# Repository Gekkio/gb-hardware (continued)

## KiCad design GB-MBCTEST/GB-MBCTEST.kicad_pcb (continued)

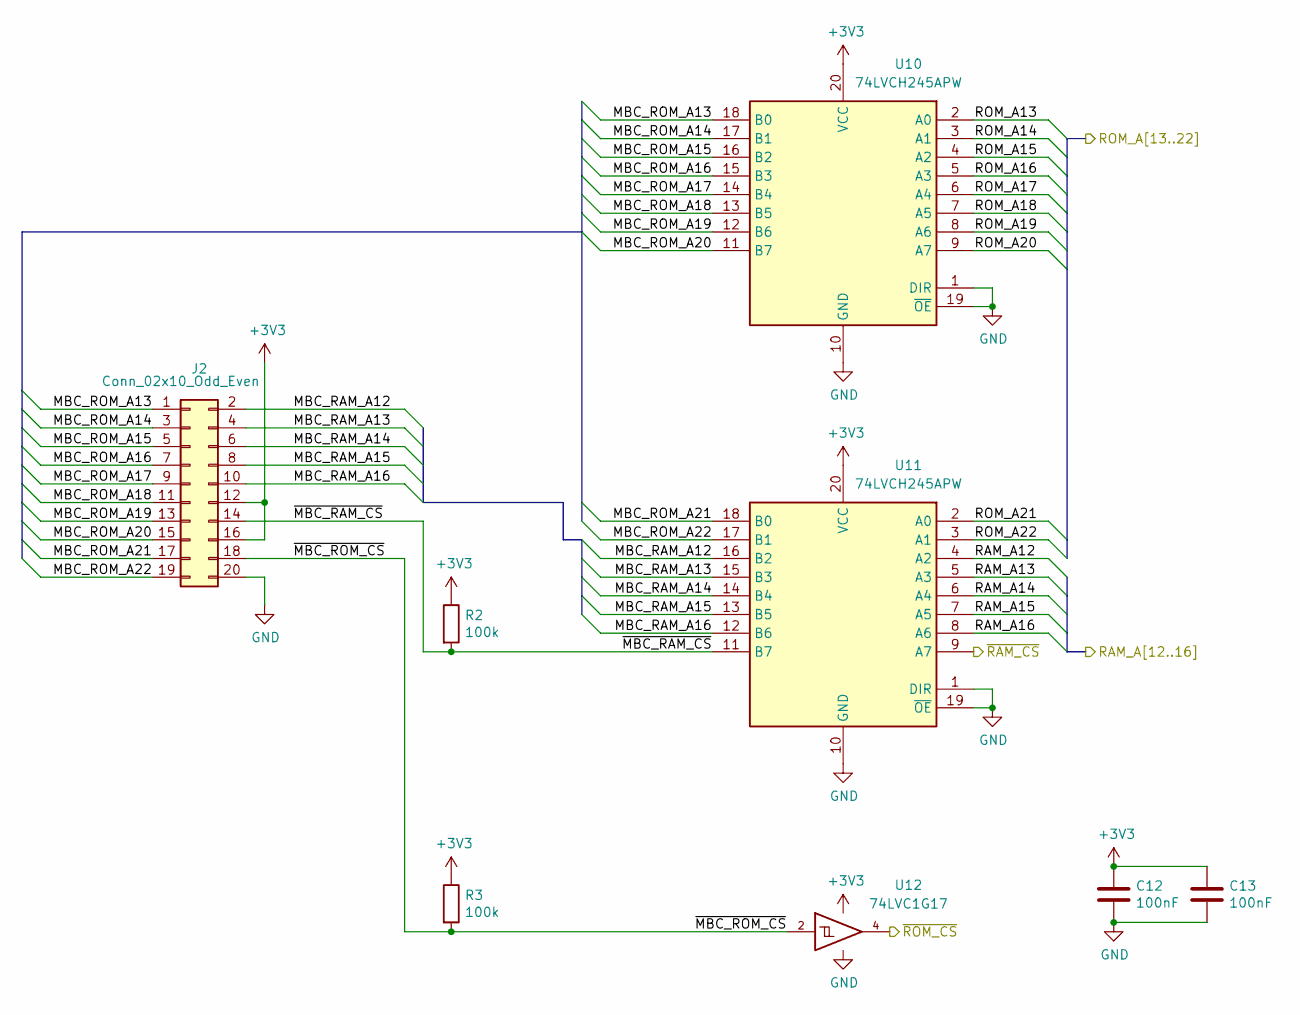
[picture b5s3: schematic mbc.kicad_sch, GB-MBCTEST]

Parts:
C12, C13: 100nF; C_0603_1608Metric
J2: Conn_02x10_Odd_Even; PinHeader_2x10_P2.54mm_Vertical_SMD
R2, R3: 100k; R_0603_1608Metric
U10, U11: 74LVCH245APW; TSSOP-20_4.4x6.5mm_P0.65mm
U12: 74LVC1G17; SOT-353_SC-70-5

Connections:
+3V3: C12.1, C13.1, J2.12, J2.16, R2.1, R3.1, U10.20 (VCC), U11.20 (VCC), U12.5 (VCC); also elsewhere on the board
/MBC/MBC_RAM_A12: J2.2, U11.16 (B2)
/MBC/MBC_RAM_A13: J2.4, U11.15 (B3)
/MBC/MBC_RAM_A14: J2.6, U11.14 (B4)
/MBC/MBC_RAM_A15: J2.8, U11.13 (B5)
/MBC/MBC_RAM_A16: J2.10, U11.12 (B6)
/MBC/MBC_ROM_A13: J2.1, U10.18 (B0)
/MBC/MBC_ROM_A14: J2.3, U10.17 (B1)
/MBC/MBC_ROM_A15: J2.5, U10.16 (B2)
/MBC/MBC_ROM_A16: J2.7, U10.15 (B3)
/MBC/MBC_ROM_A17: J2.9, U10.14 (B4)
/MBC/MBC_ROM_A18: J2.11, U10.13 (B5)
/MBC/MBC_ROM_A19: J2.13, U10.12 (B6)
/MBC/MBC_ROM_A20: J2.15, U10.11 (B7)
/MBC/MBC_ROM_A21: J2.17, U11.18 (B0)
/MBC/MBC_ROM_A22: J2.19, U11.17 (B1)
/MBC/~MBC_RAM_CS: J2.14, R2.2, U11.11 (B7)
/MBC/~MBC_ROM_CS: J2.18, R3.2, U12.2
/RAM_A12: U11.4 (A2); also elsewhere on the board
/RAM_A13: U11.5 (A3); also elsewhere on the board
/RAM_A14: U11.6 (A4); also elsewhere on the board
/RAM_A15: U11.7 (A5); also elsewhere on the board
/RAM_A16: U11.8 (A6); also elsewhere on the board
/ROM_A13: U10.2 (A0); also elsewhere on the board
/ROM_A14: U10.3 (A1); also elsewhere on the board
/ROM_A15: U10.4 (A2); also elsewhere on the board
/ROM_A16: U10.5 (A3); also elsewhere on the board
/ROM_A17: U10.6 (A4); also elsewhere on the board
/ROM_A18: U10.7 (A5); also elsewhere on the board
/ROM_A19: U10.8 (A6); also elsewhere on the board
/ROM_A20: U10.9 (A7); also elsewhere on the board
/ROM_A21: U11.2 (A0); also elsewhere on the board
/ROM_A22: U11.3 (A1); also elsewhere on the board
/~RAM_CS: U11.9 (A7); also elsewhere on the board
/~ROM_CS: U12.4; also elsewhere on the board
GND: C12.2, C13.2, J2.20, U10.1 (DIR), U10.10 (GND), U10.19 (~OE), U11.1 (DIR), U11.10 (GND), U11.19 (~OE), U12.3 (GND); also elsewhere on the board

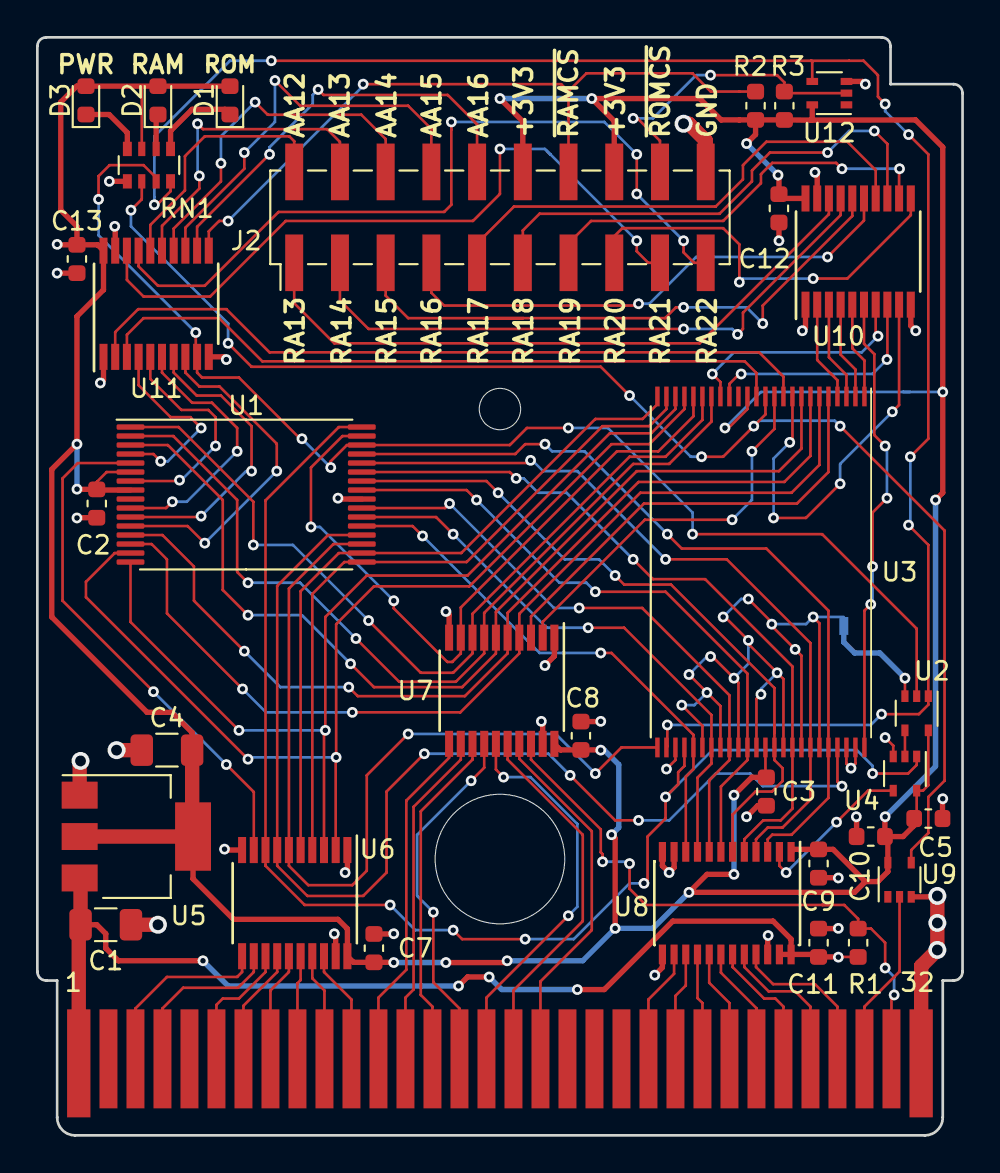
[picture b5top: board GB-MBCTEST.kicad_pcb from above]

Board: 2 copper layers, 51.4 x 61.0 mm, 36 parts (1 on the bottom side), 93 nets.

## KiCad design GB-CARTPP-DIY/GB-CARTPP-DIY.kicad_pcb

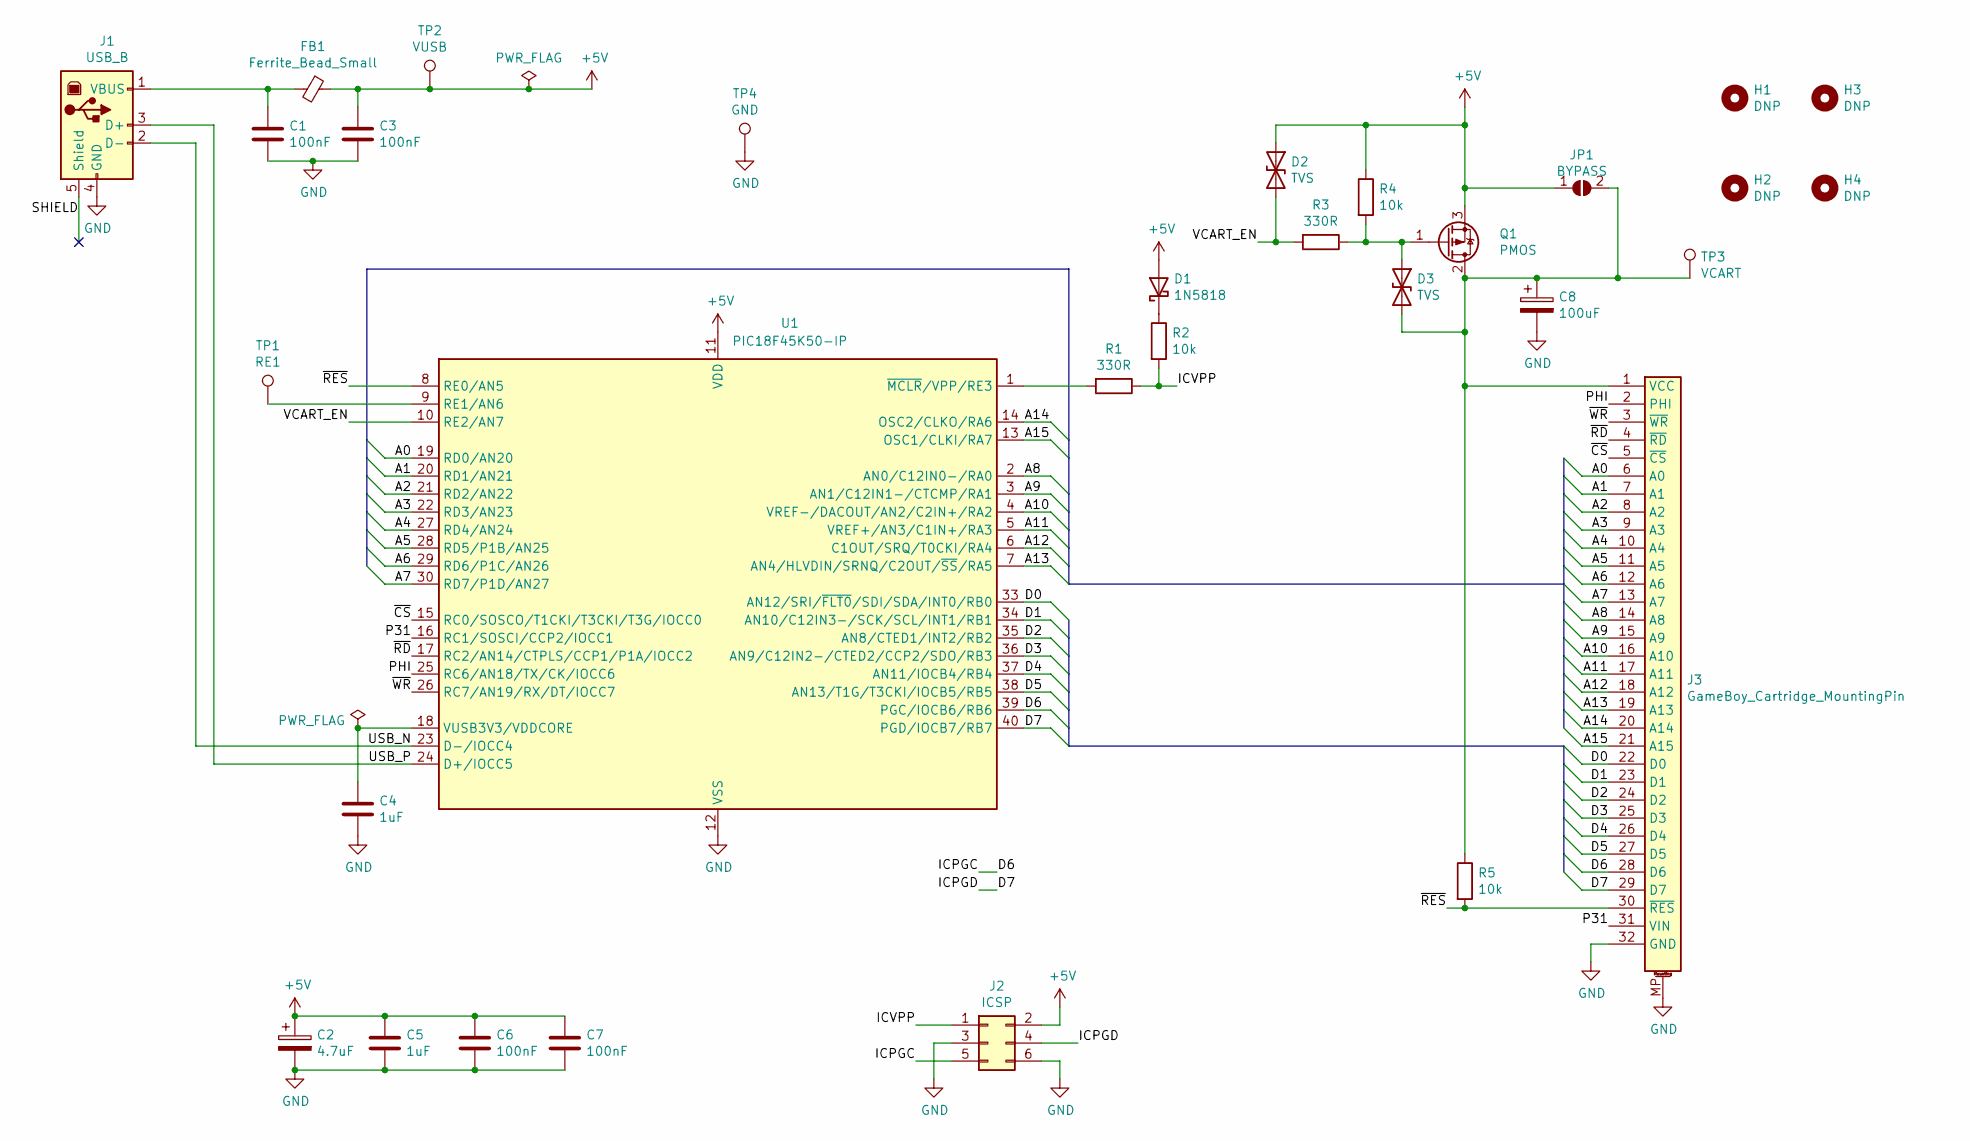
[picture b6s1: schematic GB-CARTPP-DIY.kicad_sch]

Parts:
C1, C3, C6, C7: 100nF; C_Disc_D10.5mm_W5.0mm_P5.00mm
C2: 4.7uF; CP_Radial_D6.3mm_P2.50mm
C4, C5: 1uF; C_Disc_D10.5mm_W5.0mm_P5.00mm
C8: 100uF; CP_Radial_D6.3mm_P2.50mm
D1: 1N5818; D_DO-41_SOD81_P10.16mm_Horizontal
D2, D3: TVS; D_DO-41_SOD81_P10.16mm_Horizontal
FB1: Ferrite_Bead_Small; R_Axial_DIN0411_L9.9mm_D3.6mm_P20.32mm_Horizontal
H1, H2, H3, H4: DNP; MountingHole_5.3mm_M5
J1: USB_B; USB_B_Lumberg_2411_02_Horizontal
J2: ICSP; PinHeader_2x03_P2.54mm_Vertical
J3: GameBoy_Cartridge_MountingPin; GameBoy_Cartridge_AGS_1x32-1MP_P1.50mm_Socket_Horizontal
JP1: BYPASS; SolderJumper-2_P1.3mm_Open_RoundedPad1.0x1.5mm
Q1: PMOS; TO-220-3_Vertical
R1, R3: 330R; R_Axial_DIN0207_L6.3mm_D2.5mm_P7.62mm_Horizontal
R2, R4, R5: 10k; R_Axial_DIN0207_L6.3mm_D2.5mm_P7.62mm_Horizontal
TP1: RE1; TestPoint_THTPad_D2.0mm_Drill1.0mm
TP2: VUSB; TestPoint_THTPad_D2.0mm_Drill1.0mm
TP3: VCART; TestPoint_THTPad_D2.0mm_Drill1.0mm
TP4: GND; TestPoint_THTPad_D2.0mm_Drill1.0mm
U1: PIC18F45K50-IP; DIP-40_W15.24mm_Socket_LongPads

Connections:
+5V: C2.1, C3.1, C5.1, C6.1, C7.1, D1.2 (A), D2.1 (A1), FB1.1, J2.2, JP1.1 (A), Q1.3 (S), R4.1, TP2.1, U1.11 (VDD), U1.32 (VDD)
/A0: J3.6 (A0), U1.19 (RD0/AN20)
/A1: J3.7 (A1), U1.20 (RD1/AN21)
/A2: J3.8 (A2), U1.21 (RD2/AN22)
/A3: J3.9 (A3), U1.22 (RD3/AN23)
/A4: J3.10 (A4), U1.27 (RD4/AN24)
/A5: J3.11 (A5), U1.28 (RD5/P1B/AN25)
/A6: J3.12 (A6), U1.29 (RD6/P1C/AN26)
/A7: J3.13 (A7), U1.30 (RD7/P1D/AN27)
/A8: J3.14 (A8), U1.2 (AN0/C12IN0-/RA0)
/A9: J3.15 (A9), U1.3 (AN1/C12IN1-/CTCMP/RA1)
/A10: J3.16 (A10), U1.4 (VREF-/DACOUT/AN2/C2IN+/RA2)
/A11: J3.17 (A11), U1.5 (VREF+/AN3/C1IN+/RA3)
/A12: J3.18 (A12), U1.6 (C1OUT/SRQ/T0CKI/RA4)
/A13: J3.19 (A13), U1.7 (AN4/HLVDIN/SRNQ/C2OUT/~SS/RA5)
/A14: J3.20 (A14), U1.14 (OSC2/CLKO/RA6)
/A15: J3.21 (A15), U1.13 (OSC1/CLKI/RA7)
/D0: J3.22 (D0), U1.33 (AN12/SRI/~FLT0/SDI/SDA/INT0/RB0)
/D1: J3.23 (D1), U1.34 (AN10/C12IN3-/SCK/SCL/INT1/RB1)
/D2: J3.24 (D2), U1.35 (AN8/CTED1/INT2/RB2)
/D3: J3.25 (D3), U1.36 (AN9/C12IN2-/CTED2/CCP2/SDO/RB3)
/D4: J3.26 (D4), U1.37 (AN11/IOCB4/RB4)
/D5: J3.27 (D5), U1.38 (AN13/T1G/T3CKI/IOCB5/RB5)
/D6: J2.5, J3.28 (D6), U1.39 (PGC/IOCB6/RB6)
/D7: J2.4, J3.29 (D7), U1.40 (PGD/IOCB7/RB7)
/ICVPP: J2.1, R1.1, R2.2
/P31: J3.31 (VIN), U1.16 (RC1/SOSCI/CCP2/IOCC1)
/PHI: J3.2 (PHI), U1.25 (RC6/AN18/TX/CK/IOCC6)
/SHIELD: J1.5 (Shield)
/USB_N: J1.2 (D-), U1.23 (D-/IOCC4)
/USB_P: J1.3 (D+), U1.24 (D+/IOCC5)
/VCART_EN: D2.2 (A2), R3.2, U1.10 (RE2/AN7)
/~CS: J3.5 (~CS), U1.15 (RC0/SOSCO/T1CKI/T3CKI/T3G/IOCC0)
/~RD: J3.4 (~RD), U1.17 (RC2/AN14/CTPLS/CCP1/P1A/IOCC2)
/~RES: J3.30 (~RES), R5.2, U1.8 (RE0/AN5)
/~WR: J3.3 (~WR), U1.26 (RC7/AN19/RX/DT/IOCC7)
GND: C1.2, C2.2, C3.2, C4.2, C5.2, C6.2, C7.2, C8.2, J1.4 (GND), J2.3, J2.6, J3.32 (GND), J3.MP, TP4.1, U1.12 (VSS), U1.31 (VSS)
unnamed: C1.1, FB1.2, J1.1 (VBUS)
unnamed: C4.1, U1.18 (VUSB3V3/VDDCORE)
unnamed: C8.1, D3.2 (A2), J3.1 (VCC), JP1.2 (B), Q1.2 (D), R5.1, TP3.1
unnamed: D1.1 (K), R2.1
unnamed: D3.1 (A1), Q1.1 (G), R3.1, R4.2
unnamed: R1.2, U1.1 (~MCLR/VPP/RE3)
unnamed: TP1.1, U1.9 (RE1/AN6)

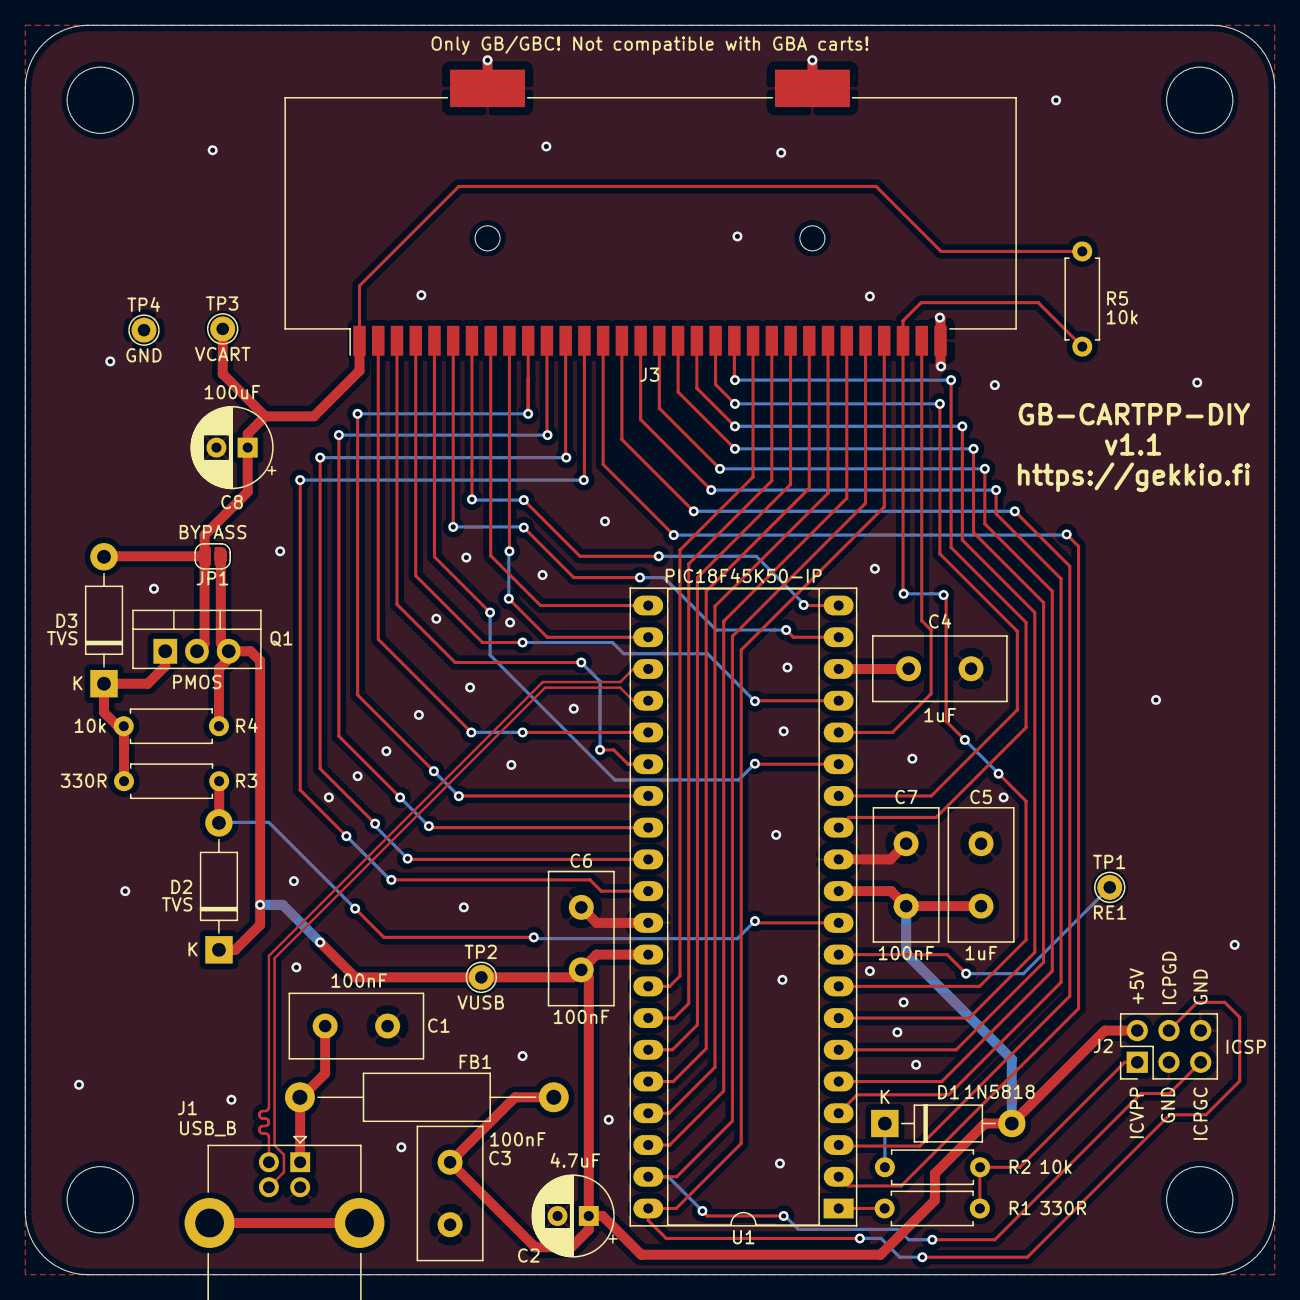
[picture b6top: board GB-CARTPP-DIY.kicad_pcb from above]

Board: 2 copper layers, 100.0 x 100.0 mm, 31 parts (0 on the bottom side), 43 nets.

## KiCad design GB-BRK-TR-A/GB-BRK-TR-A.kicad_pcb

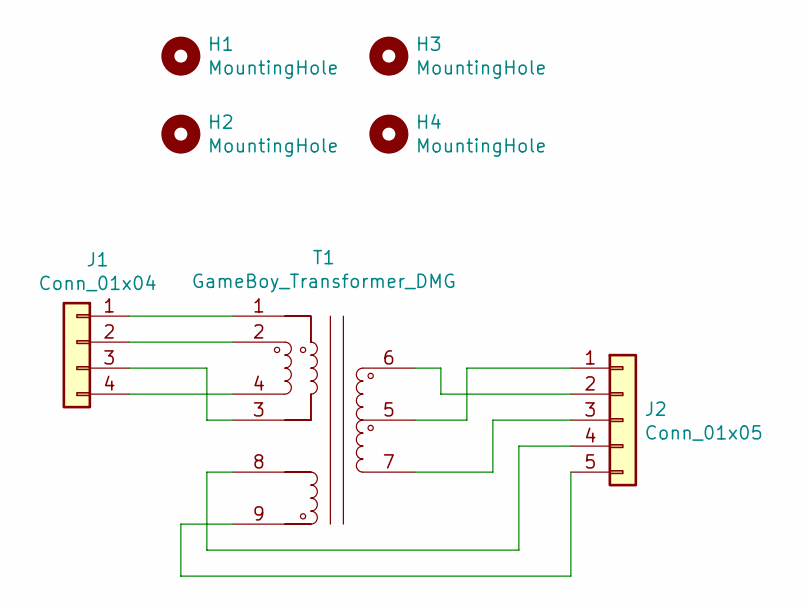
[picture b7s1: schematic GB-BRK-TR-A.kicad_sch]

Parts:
H1, H2, H3, H4: MountingHole; MountingHole_3.2mm_M3
J1: Conn_01x04; PinHeader_1x04_P2.54mm_Vertical
J2: Conn_01x05; PinHeader_1x05_P2.54mm_Vertical
T1: GameBoy_Transformer_DMG; Transformer_GameBoy_DMG

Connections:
unnamed: J1.1, T1.1
unnamed: J1.2, T1.2
unnamed: J1.3, T1.3
unnamed: J1.4, T1.4
unnamed: J2.1, T1.5
unnamed: J2.2, T1.6
unnamed: J2.3, T1.7
unnamed: J2.4, T1.8
unnamed: J2.5, T1.9

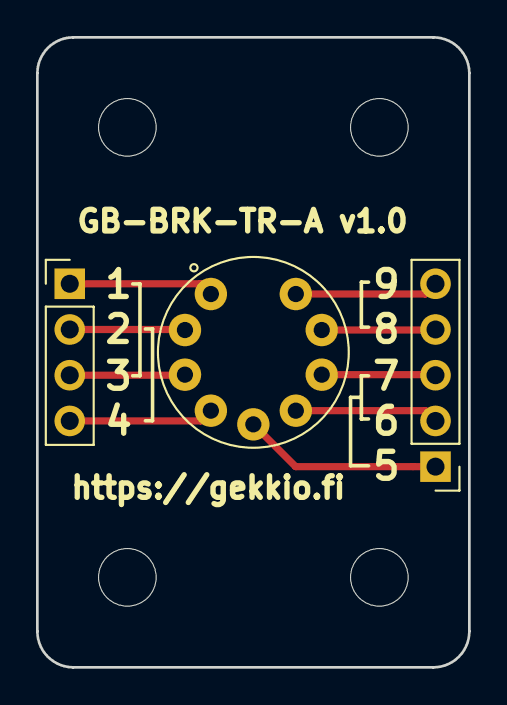
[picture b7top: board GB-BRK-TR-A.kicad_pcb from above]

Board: 2 copper layers, 24.0 x 35.0 mm, 7 parts (0 on the bottom side), 9 nets.

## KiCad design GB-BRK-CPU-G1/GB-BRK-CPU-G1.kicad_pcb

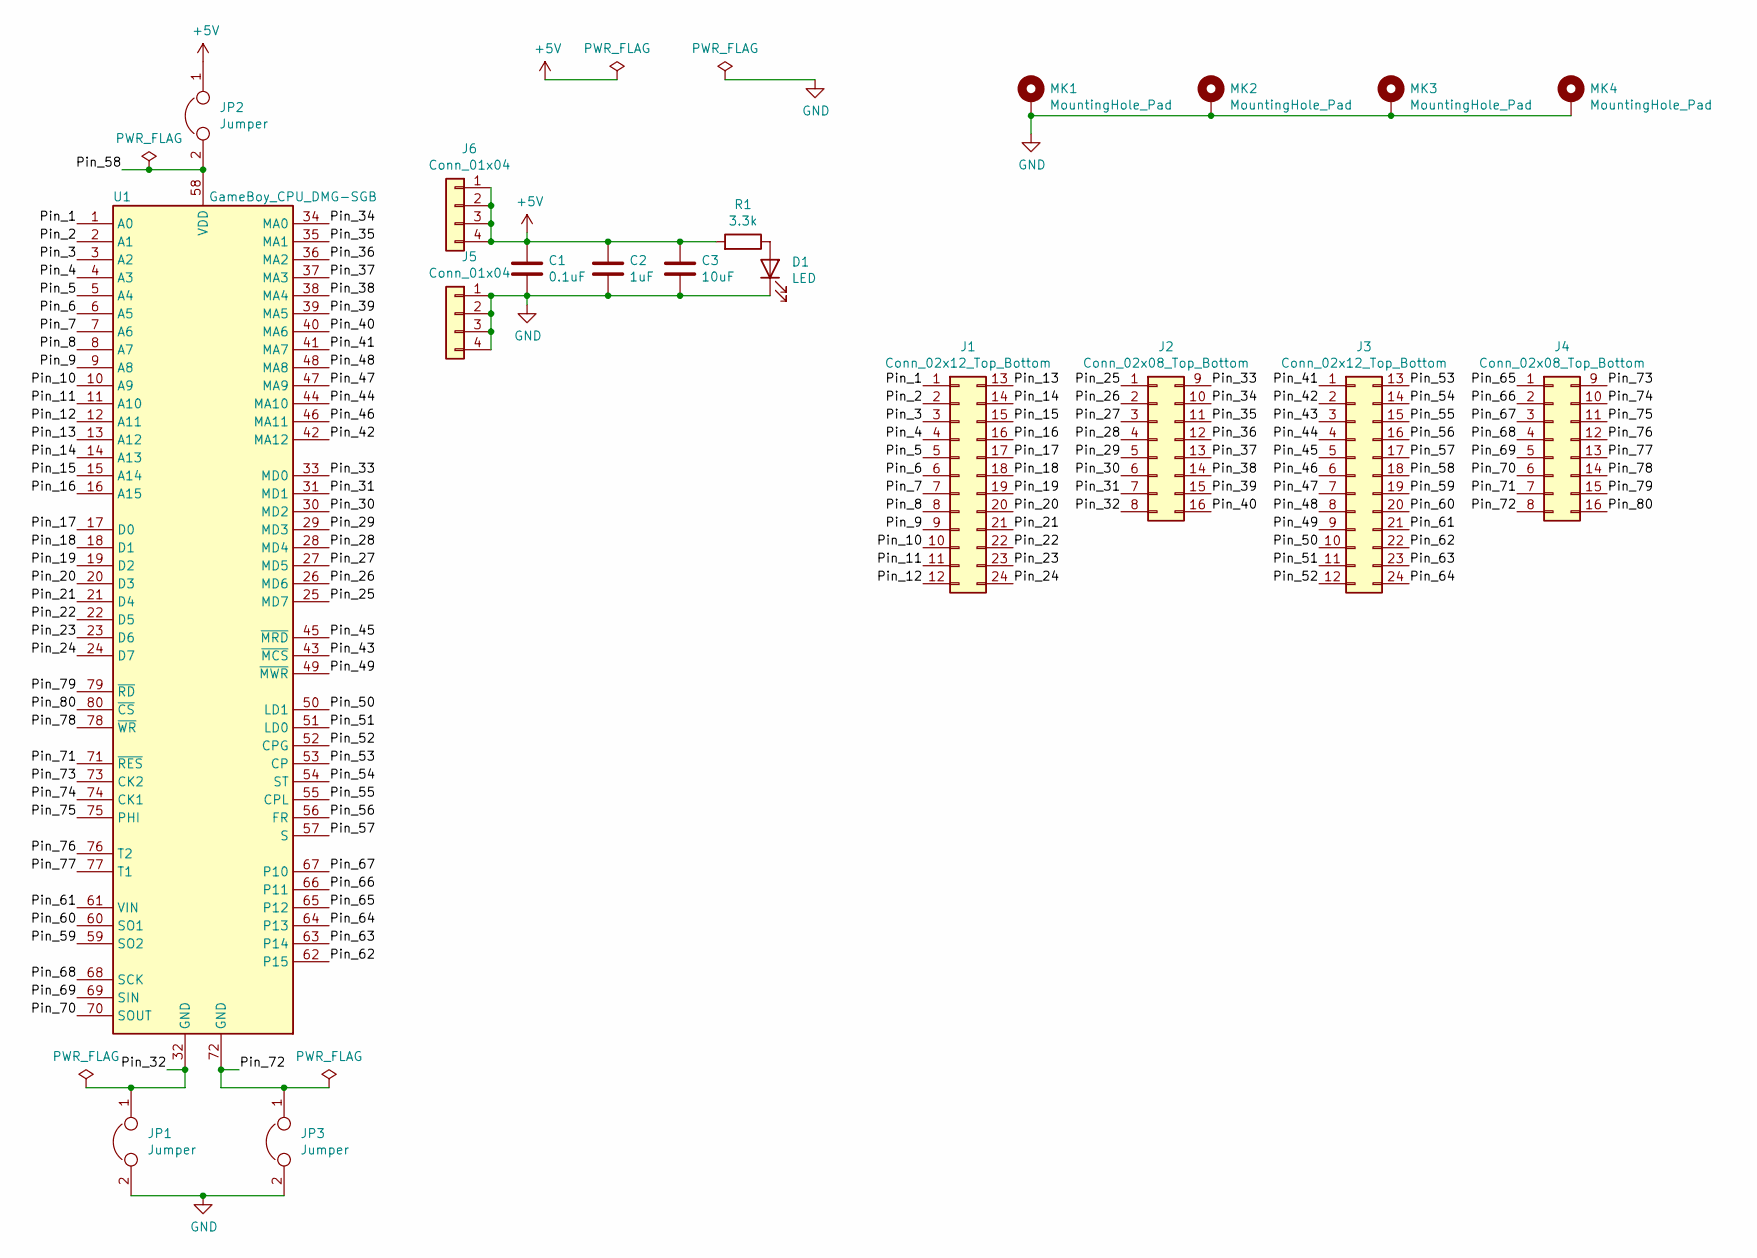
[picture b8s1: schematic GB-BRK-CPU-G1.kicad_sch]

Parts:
C1: 0.1uF; C_0603_1608Metric
C2: 1uF; C_0805_2012Metric
C3: 10uF; C_1206_3216Metric
D1: LED; LED_0603_1608Metric
J1, J3: Conn_02x12_Top_Bottom; PinHeader_2x12_P2.54mm_Vertical
J2, J4: Conn_02x08_Top_Bottom; PinHeader_2x08_P2.54mm_Vertical
J5, J6: Conn_01x04; PinHeader_1x04_P2.54mm_Vertical
JP1, JP2, JP3: Jumper; SolderJumper-2_P1.3mm_Open_TrianglePad1.0x1.5mm
MK1, MK2, MK3, MK4: MountingHole_Pad; MountingHole_3.2mm_M3_Pad_Via
R1: 3.3k; R_0603_1608Metric
U1: GameBoy_CPU_DMG-SGB; Sharp_QFP-80_14x20mm_P0.8mm

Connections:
+5V: C1.1, C2.1, C3.1, J6.1, J6.2, J6.3, J6.4, JP2.1, R1.2
/Pin_1: J1.1, U1.1 (A0)
/Pin_2: J1.2, U1.2 (A1)
/Pin_3: J1.3, U1.3 (A2)
/Pin_4: J1.4, U1.4 (A3)
/Pin_5: J1.5, U1.5 (A4)
/Pin_6: J1.6, U1.6 (A5)
/Pin_7: J1.7, U1.7 (A6)
/Pin_8: J1.8, U1.8 (A7)
/Pin_9: J1.9, U1.9 (A8)
/Pin_10: J1.10, U1.10 (A9)
/Pin_11: J1.11, U1.11 (A10)
/Pin_12: J1.12, U1.12 (A11)
/Pin_13: J1.13, U1.13 (A12)
/Pin_14: J1.14, U1.14 (A13)
/Pin_15: J1.15, U1.15 (A14)
/Pin_16: J1.16, U1.16 (A15)
/Pin_17: J1.17, U1.17 (D0)
/Pin_18: J1.18, U1.18 (D1)
/Pin_19: J1.19, U1.19 (D2)
/Pin_20: J1.20, U1.20 (D3)
/Pin_21: J1.21, U1.21 (D4)
/Pin_22: J1.22, U1.22 (D5)
/Pin_23: J1.23, U1.23 (D6)
/Pin_24: J1.24, U1.24 (D7)
/Pin_25: J2.1, U1.25 (MD7)
/Pin_26: J2.2, U1.26 (MD6)
/Pin_27: J2.3, U1.27 (MD5)
/Pin_28: J2.4, U1.28 (MD4)
/Pin_29: J2.5, U1.29 (MD3)
/Pin_30: J2.6, U1.30 (MD2)
/Pin_31: J2.7, U1.31 (MD1)
/Pin_32: J2.8, JP1.1, U1.32 (GND)
/Pin_33: J2.9, U1.33 (MD0)
/Pin_34: J2.10, U1.34 (MA0)
/Pin_35: J2.11, U1.35 (MA1)
/Pin_36: J2.12, U1.36 (MA2)
/Pin_37: J2.13, U1.37 (MA3)
/Pin_38: J2.14, U1.38 (MA4)
/Pin_39: J2.15, U1.39 (MA5)
/Pin_40: J2.16, U1.40 (MA6)
/Pin_41: J3.1, U1.41 (MA7)
/Pin_42: J3.2, U1.42 (MA12)
/Pin_43: J3.3, U1.43 (~MCS)
/Pin_44: J3.4, U1.44 (MA10)
/Pin_45: J3.5, U1.45 (~MRD)
/Pin_46: J3.6, U1.46 (MA11)
/Pin_47: J3.7, U1.47 (MA9)
/Pin_48: J3.8, U1.48 (MA8)
/Pin_49: J3.9, U1.49 (~MWR)
/Pin_50: J3.10, U1.50 (LD1)
/Pin_51: J3.11, U1.51 (LD0)
/Pin_52: J3.12, U1.52 (CPG)
/Pin_53: J3.13, U1.53 (CP)
/Pin_54: J3.14, U1.54 (ST)
/Pin_55: J3.15, U1.55 (CPL)
/Pin_56: J3.16, U1.56 (FR)
/Pin_57: J3.17, U1.57 (S)
/Pin_58: J3.18, JP2.2, U1.58 (VDD)
/Pin_59: J3.19, U1.59 (SO2)
/Pin_60: J3.20, U1.60 (SO1)
/Pin_61: J3.21, U1.61 (VIN)
/Pin_62: J3.22, U1.62 (P15)
/Pin_63: J3.23, U1.63 (P14)
/Pin_64: J3.24, U1.64 (P13)
/Pin_65: J4.1, U1.65 (P12)
/Pin_66: J4.2, U1.66 (P11)
/Pin_67: J4.3, U1.67 (P10)
/Pin_68: J4.4, U1.68 (SCK)
/Pin_69: J4.5, U1.69 (SIN)
/Pin_70: J4.6, U1.70 (SOUT)
/Pin_71: J4.7, U1.71 (~RES)
/Pin_72: J4.8, JP3.1, U1.72 (GND)
/Pin_73: J4.9, U1.73 (CK2)
/Pin_74: J4.10, U1.74 (CK1)
/Pin_75: J4.11, U1.75 (PHI)
/Pin_76: J4.12, U1.76 (T2)
/Pin_77: J4.13, U1.77 (T1)
/Pin_78: J4.14, U1.78 (~WR)
/Pin_79: J4.15, U1.79 (~RD)
/Pin_80: J4.16, U1.80 (~CS)
GND: C1.2, C2.2, C3.2, D1.1 (K), J5.1, J5.2, J5.3, J5.4, JP1.2, JP3.2, MK1.1, MK2.1, MK3.1, MK4.1
unnamed: D1.2 (A), R1.1

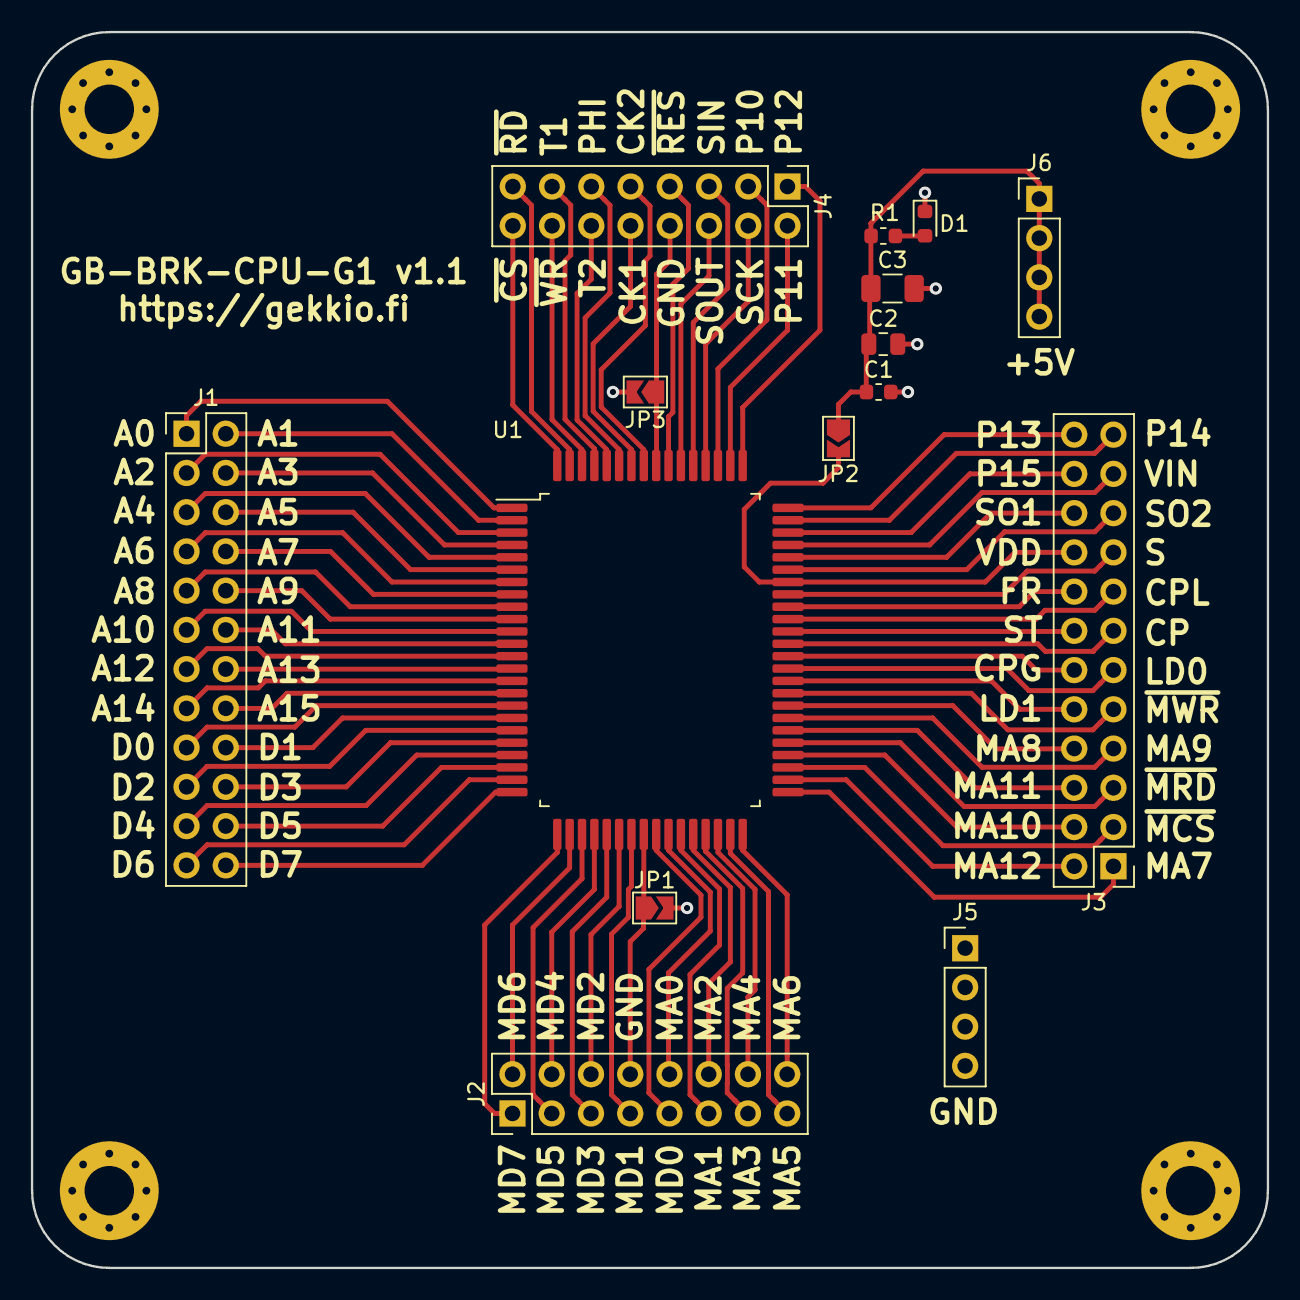
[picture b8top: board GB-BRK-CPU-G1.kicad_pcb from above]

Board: 2 copper layers, 80.0 x 80.0 mm, 19 parts (0 on the bottom side), 83 nets.

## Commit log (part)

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2015-08-13 GB-BRK-F v1.0
2015-08-13 Add README
2015-08-13 Add photos to README
2015-08-13 Add TODO
2015-08-13 More TODO
2016-06-16 Ignore some temporary files
2016-06-16 GB-BRK-M v2.1
2016-06-16 GB-BRK-M Board layout, mention ground plane
2016-06-16 GB-BRK-M v2.1 photo
2017-09-03 GB-BRK-M v3.0
2017-09-10 Add GB-BRK-M v3.0 Mouser project link
2017-10-03 GB-BENCH-G1 v1.0
2017-12-12 Use symbols from kicad-library submodule
2018-02-15 GB-BRK-M v3.1
2018-02-15 GB-BRK-M-XS v1.0 + restructuring
2018-02-15 Get rid of old submodule structure
2018-02-15 Oops :O
2018-07-04 GB-BRK-CART v4.0, GB-LIVE32 v2.0
2018-07-09 Minor fixes + add schematic
2018-07-09 Goodbye GB-BRK-M
2018-07-09 More details and fixes
2018-07-09 Oops
2018-07-11 BOM + docs
2018-07-11 More BOM stuff
2018-07-18 Stop recommending bus hold transceivers for GB-LIVE32 boards
2018-07-28 GB-BRK-CPU-G1, GB-BRK-CPU-G2
2019-01-02 GB-BRK-LINK-A, GB-BRK-SLOT-A
2019-01-02 GB-CART2M-A
2019-01-02 Fix schematics broken after library updates
2019-01-02 Goodbye GB-BRK-F
2019-01-05 Update GB-BRK-SLOT-A libs
2019-01-05 Update PCB size and thickness recommendations
2019-06-20 Ignore fp-info-cache
2019-06-20 Add GB-CART2M-A v1.1
2019-06-20 Add GB-BRK-LINK-B v1.0
2019-06-20 Add GB-CART32K-A v1.0
2019-06-20 Optimize with optipng
2019-06-20 Add GB-CART32K-A to README
2020-02-14 Ignore schematic backups
2020-02-14 Update GB-BRK-CPU-G1/G2
2020-02-14 Add GB-BRK-TR-A v1.0
2020-02-14 Rename CART2M -> CART256K, update libs
2020-02-14 Update GB-CART32K-A
2020-02-14 Fix version number in README
2020-02-14 Add firmware/software links
2020-02-14 Add GB-MBCTEST v1.1
2020-02-14 Add GB-BRK-SLOT-B v1.0
2020-02-25 Use a different submodule setup
2020-02-25 Refresh board 3d images
2020-05-17 Set solder mask min width to 0, regenerate gerbers
2020-10-04 Restore old submodule setup
2020-10-04 Add GB-CARTPP-XC v1.2
2020-10-04 Add GB-CARTPP-DIY v1.1
2020-10-04 Remove git submodules
2020-10-04 Squashed 'GB-BENCH-G1/external/gekkio-kicad-libs/' content from commit 11c755d
    git-subtree-dir: GB-BENCH-G1/external/gekkio-kicad-libs
    git-subtree-split: 11c755dfcdc33b887ce2f8f05dc104d8bac43b0a
2020-10-04 Squashed 'GB-BRK-CART/external/gekkio-kicad-libs/' content from commit 68ff78c
    git-subtree-dir: GB-BRK-CART/external/gekkio-kicad-libs
    git-subtree-split: 68ff78c677faf7e9ad431e0bda488bada8557420
2020-10-04 Squashed 'GB-BRK-CART/external/kicad-footprints/' content from commit 93c1f36d
    git-subtree-dir: GB-BRK-CART/external/kicad-footprints
    git-subtree-split: 93c1f36d7492bccb005f4b87ee5bbf2226d03d07
2020-10-04 Squashed 'GB-BRK-CART/external/kicad-symbols/' content from commit db28d85f
    git-subtree-dir: GB-BRK-CART/external/kicad-symbols
    git-subtree-split: db28d85faa814b910e2a16dc6368c1c45187a65d
2020-10-04 Squashed 'GB-BRK-CPU-G1/external/gekkio-kicad-libs/' content from commit edbc4af9
    git-subtree-dir: GB-BRK-CPU-G1/external/gekkio-kicad-libs
    git-subtree-split: edbc4af957fb373c6f8487669a449dabef35f812
2020-10-04 Squashed 'GB-BRK-CPU-G1/external/kicad-footprints/' content from commit db28d85fa
    git-subtree-dir: GB-BRK-CPU-G1/external/kicad-footprints
    git-subtree-split: db28d85faa814b910e2a16dc6368c1c45187a65d
2020-10-04 Squashed 'GB-BRK-CPU-G1/external/kicad-symbols/' content from commit 6127141df
    git-subtree-dir: GB-BRK-CPU-G1/external/kicad-symbols
    git-subtree-split: 6127141dfa6cc83758da58333c4871d682af609c
2020-10-04 Squashed 'GB-BRK-CPU-G2/external/gekkio-kicad-libs/' content from commit edbc4af95
    git-subtree-dir: GB-BRK-CPU-G2/external/gekkio-kicad-libs
    git-subtree-split: edbc4af957fb373c6f8487669a449dabef35f812
2020-10-04 Squashed 'GB-BRK-CPU-G2/external/kicad-footprints/' content from commit ef28214e0
    git-subtree-dir: GB-BRK-CPU-G2/external/kicad-footprints
    git-subtree-split: ef28214e02a0807a5262ed7afe9995762211f28e
2020-10-04 Squashed 'GB-BRK-LINK-A/external/gekkio-kicad-libs/' content from commit ab5ed93c4
    git-subtree-dir: GB-BRK-LINK-A/external/gekkio-kicad-libs
    git-subtree-split: ab5ed93c455c0355b77c4fd9823f606ef7e62302
2020-10-04 Squashed 'GB-BRK-LINK-A/external/kicad-footprints/' content from commit 73119a614
    git-subtree-dir: GB-BRK-LINK-A/external/kicad-footprints
    git-subtree-split: 73119a614f1d35dd87a1b701d7ea77b9698b41d5
2020-10-04 Squashed 'GB-BRK-LINK-A/external/kicad-symbols/' content from commit 6a196c145
    git-subtree-dir: GB-BRK-LINK-A/external/kicad-symbols
    git-subtree-split: 6a196c1457989e8584a95669e2d033e11d83a31d
2020-10-04 Squashed 'GB-BRK-LINK-B/external/gekkio-kicad-libs/' content from commit 8721ad5c9
    git-subtree-dir: GB-BRK-LINK-B/external/gekkio-kicad-libs
    git-subtree-split: 8721ad5c9ea095d1bb754207a810c6bdbffe65f8
2020-10-04 Squashed 'GB-BRK-LINK-B/external/kicad-footprints/' content from commit 6015d7b7b
    git-subtree-dir: GB-BRK-LINK-B/external/kicad-footprints
    git-subtree-split: 6015d7b7b8af2527c2e7a8be9f9f652ea64fbd4d
2020-10-04 Squashed 'GB-BRK-LINK-B/external/kicad-symbols/' content from commit 674655e9f
    git-subtree-dir: GB-BRK-LINK-B/external/kicad-symbols
    git-subtree-split: 674655e9f35b3db56f24f55d6f0971510d0e71c5
2020-10-04 Squashed 'GB-BRK-M-XS/external/gekkio-kicad-libs/' content from commit d15bb29f4
    git-subtree-dir: GB-BRK-M-XS/external/gekkio-kicad-libs
    git-subtree-split: d15bb29f43356d5c0c9f6acf63060d8015be227a
2020-10-04 Squashed 'GB-BRK-M-XS/external/kicad-footprints/' content from commit c42a76b78
    git-subtree-dir: GB-BRK-M-XS/external/kicad-footprints
    git-subtree-split: c42a76b78466583bd626f54cd52a304959612dfd
2020-10-04 Squashed 'GB-BRK-M-XS/external/kicad-symbols/' content from commit 41be9dd93
    git-subtree-dir: GB-BRK-M-XS/external/kicad-symbols
    git-subtree-split: 41be9dd9385a58e37a00dbbb61f88c1f826a0727
2020-10-04 Squashed 'GB-BRK-SLOT-A/external/gekkio-kicad-libs/' content from commit aab0c6a23
    git-subtree-dir: GB-BRK-SLOT-A/external/gekkio-kicad-libs
    git-subtree-split: aab0c6a234ac117c6bacdfbf41116c055d695e5b
2020-10-04 Squashed 'GB-BRK-SLOT-A/external/kicad-footprints/' content from commit ef28214e0
    git-subtree-dir: GB-BRK-SLOT-A/external/kicad-footprints
    git-subtree-split: ef28214e02a0807a5262ed7afe9995762211f28e
2020-10-04 Squashed 'GB-BRK-SLOT-A/external/kicad-symbols/' content from commit 6127141df
    git-subtree-dir: GB-BRK-SLOT-A/external/kicad-symbols
    git-subtree-split: 6127141dfa6cc83758da58333c4871d682af609c
2020-10-04 Squashed 'GB-BRK-SLOT-B/external/gekkio-kicad-libs/' content from commit aab0c6a23
    git-subtree-dir: GB-BRK-SLOT-B/external/gekkio-kicad-libs
    git-subtree-split: aab0c6a234ac117c6bacdfbf41116c055d695e5b
2020-10-04 Squashed 'GB-BRK-SLOT-B/external/kicad-footprints/' content from commit ef28214e0
    git-subtree-dir: GB-BRK-SLOT-B/external/kicad-footprints
    git-subtree-split: ef28214e02a0807a5262ed7afe9995762211f28e
2020-10-04 Squashed 'GB-BRK-SLOT-B/external/kicad-symbols/' content from commit 6127141df
    git-subtree-dir: GB-BRK-SLOT-B/external/kicad-symbols
    git-subtree-split: 6127141dfa6cc83758da58333c4871d682af609c
2020-10-04 Squashed 'GB-BRK-TR-A/external/kicad-footprints/' content from commit ef28214e0
    git-subtree-dir: GB-BRK-TR-A/external/kicad-footprints
    git-subtree-split: ef28214e02a0807a5262ed7afe9995762211f28e
2020-10-04 Squashed 'GB-BRK-TR-A/external/kicad-symbols/' content from commit 6127141df
    git-subtree-dir: GB-BRK-TR-A/external/kicad-symbols
    git-subtree-split: 6127141dfa6cc83758da58333c4871d682af609c
2020-10-04 Squashed 'GB-CART256K-A/external/gekkio-kicad-libs/' content from commit edbc4af95
    git-subtree-dir: GB-CART256K-A/external/gekkio-kicad-libs
    git-subtree-split: edbc4af957fb373c6f8487669a449dabef35f812
2020-10-04 Squashed 'GB-CART256K-A/external/kicad-footprints/' content from commit ef28214e0
    git-subtree-dir: GB-CART256K-A/external/kicad-footprints
    git-subtree-split: ef28214e02a0807a5262ed7afe9995762211f28e
2020-10-04 Squashed 'GB-CART256K-A/external/kicad-symbols/' content from commit 6127141df
    git-subtree-dir: GB-CART256K-A/external/kicad-symbols
    git-subtree-split: 6127141dfa6cc83758da58333c4871d682af609c
2020-10-04 Squashed 'GB-CART32K-A/external/gekkio-kicad-libs/' content from commit edbc4af95
    git-subtree-dir: GB-CART32K-A/external/gekkio-kicad-libs
    git-subtree-split: edbc4af957fb373c6f8487669a449dabef35f812
2020-10-04 Squashed 'GB-CART32K-A/external/kicad-footprints/' content from commit ef28214e0
    git-subtree-dir: GB-CART32K-A/external/kicad-footprints
    git-subtree-split: ef28214e02a0807a5262ed7afe9995762211f28e
2020-10-04 Squashed 'GB-CART32K-A/external/kicad-symbols/' content from commit 6127141df
    git-subtree-dir: GB-CART32K-A/external/kicad-symbols
    git-subtree-split: 6127141dfa6cc83758da58333c4871d682af609c
2020-10-04 Squashed 'GB-CARTPP-DIY/external/gekkio-kicad-libs/' content from commit 2919aa0b7
    git-subtree-dir: GB-CARTPP-DIY/external/gekkio-kicad-libs
    git-subtree-split: 2919aa0b720b1052a1768f17334fa5c2c270bbf9
2020-10-04 Squashed 'GB-CARTPP-DIY/external/kicad-footprints/' content from commit e5d039f23
    git-subtree-dir: GB-CARTPP-DIY/external/kicad-footprints
    git-subtree-split: e5d039f23699e97957c205c386c82ee7433470f3
2020-10-04 Squashed 'GB-CARTPP-DIY/external/kicad-symbols/' content from commit db28d85fa
    git-subtree-dir: GB-CARTPP-DIY/external/kicad-symbols
    git-subtree-split: db28d85faa814b910e2a16dc6368c1c45187a65d
2020-10-04 Squashed 'GB-CARTPP-XC/external/gekkio-kicad-libs/' content from commit 2919aa0b7
    git-subtree-dir: GB-CARTPP-XC/external/gekkio-kicad-libs
    git-subtree-split: 2919aa0b720b1052a1768f17334fa5c2c270bbf9
2020-10-04 Squashed 'GB-CARTPP-XC/external/kicad-footprints/' content from commit e5d039f23
    git-subtree-dir: GB-CARTPP-XC/external/kicad-footprints
    git-subtree-split: e5d039f23699e97957c205c386c82ee7433470f3
2020-10-04 Squashed 'GB-CARTPP-XC/external/kicad-symbols/' content from commit c5e86f1ea
    git-subtree-dir: GB-CARTPP-XC/external/kicad-symbols
    git-subtree-split: c5e86f1ea7a8f0ef7a75cacc0d83d27cf8b718e4
2020-10-04 Squashed 'GB-LIVE32/external/gekkio-kicad-libs/' content from commit 68ff78c67
    git-subtree-dir: GB-LIVE32/external/gekkio-kicad-libs
    git-subtree-split: 68ff78c677faf7e9ad431e0bda488bada8557420
2020-10-04 Squashed 'GB-LIVE32/external/kicad-footprints/' content from commit 93c1f36d7
    git-subtree-dir: GB-LIVE32/external/kicad-footprints
    git-subtree-split: 93c1f36d7492bccb005f4b87ee5bbf2226d03d07
2020-10-04 Squashed 'GB-MBCTEST/external/gekkio-kicad-libs/' content from commit aab0c6a23
    git-subtree-dir: GB-MBCTEST/external/gekkio-kicad-libs
    git-subtree-split: aab0c6a234ac117c6bacdfbf41116c055d695e5b
2020-10-04 Squashed 'GB-MBCTEST/external/kicad-footprints/' content from commit ef28214e0
    git-subtree-dir: GB-MBCTEST/external/kicad-footprints
    git-subtree-split: ef28214e02a0807a5262ed7afe9995762211f28e
2020-10-04 Squashed 'GB-MBCTEST/external/kicad-symbols/' content from commit 6127141df
    git-subtree-dir: GB-MBCTEST/external/kicad-symbols
    git-subtree-split: 6127141dfa6cc83758da58333c4871d682af609c
2021-02-06 Remove broken subtree
2021-02-06 Squashed 'GB-BRK-CART/external/kicad-symbols/' content from commit 68774423
    git-subtree-dir: GB-BRK-CART/external/kicad-symbols
    git-subtree-split: 68774423231dbe8834010941e1d220b286c20071
2021-02-06 Remove broken subtrees
2021-02-06 Squashed 'GB-CARTPP-DIY/external/kicad-symbols/' content from commit c5e86f1e
    git-subtree-dir: GB-CARTPP-DIY/external/kicad-symbols
    git-subtree-split: c5e86f1ea7a8f0ef7a75cacc0d83d27cf8b718e4
2021-02-06 Squashed 'GB-BRK-CPU-G1/external/kicad-footprints/' content from commit ef28214e0
    git-subtree-dir: GB-BRK-CPU-G1/external/kicad-footprints
    git-subtree-split: ef28214e02a0807a5262ed7afe9995762211f28e
2022-05-07 Add naughty list
2022-09-11 Upgrade most projects to KiCad 6
2022-09-11 Rescue GB-BRK-M-XS and convert to KiCad 6
2022-09-11 Rescue GB-BENCH-G1 and convert to KiCad 6
2023-07-20 Upgrade projects to KiCad 7
